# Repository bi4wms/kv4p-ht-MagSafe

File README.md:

# kv4p-ht-MagSafe
MagSafe version for kv4p-ht. Work in progress.

---

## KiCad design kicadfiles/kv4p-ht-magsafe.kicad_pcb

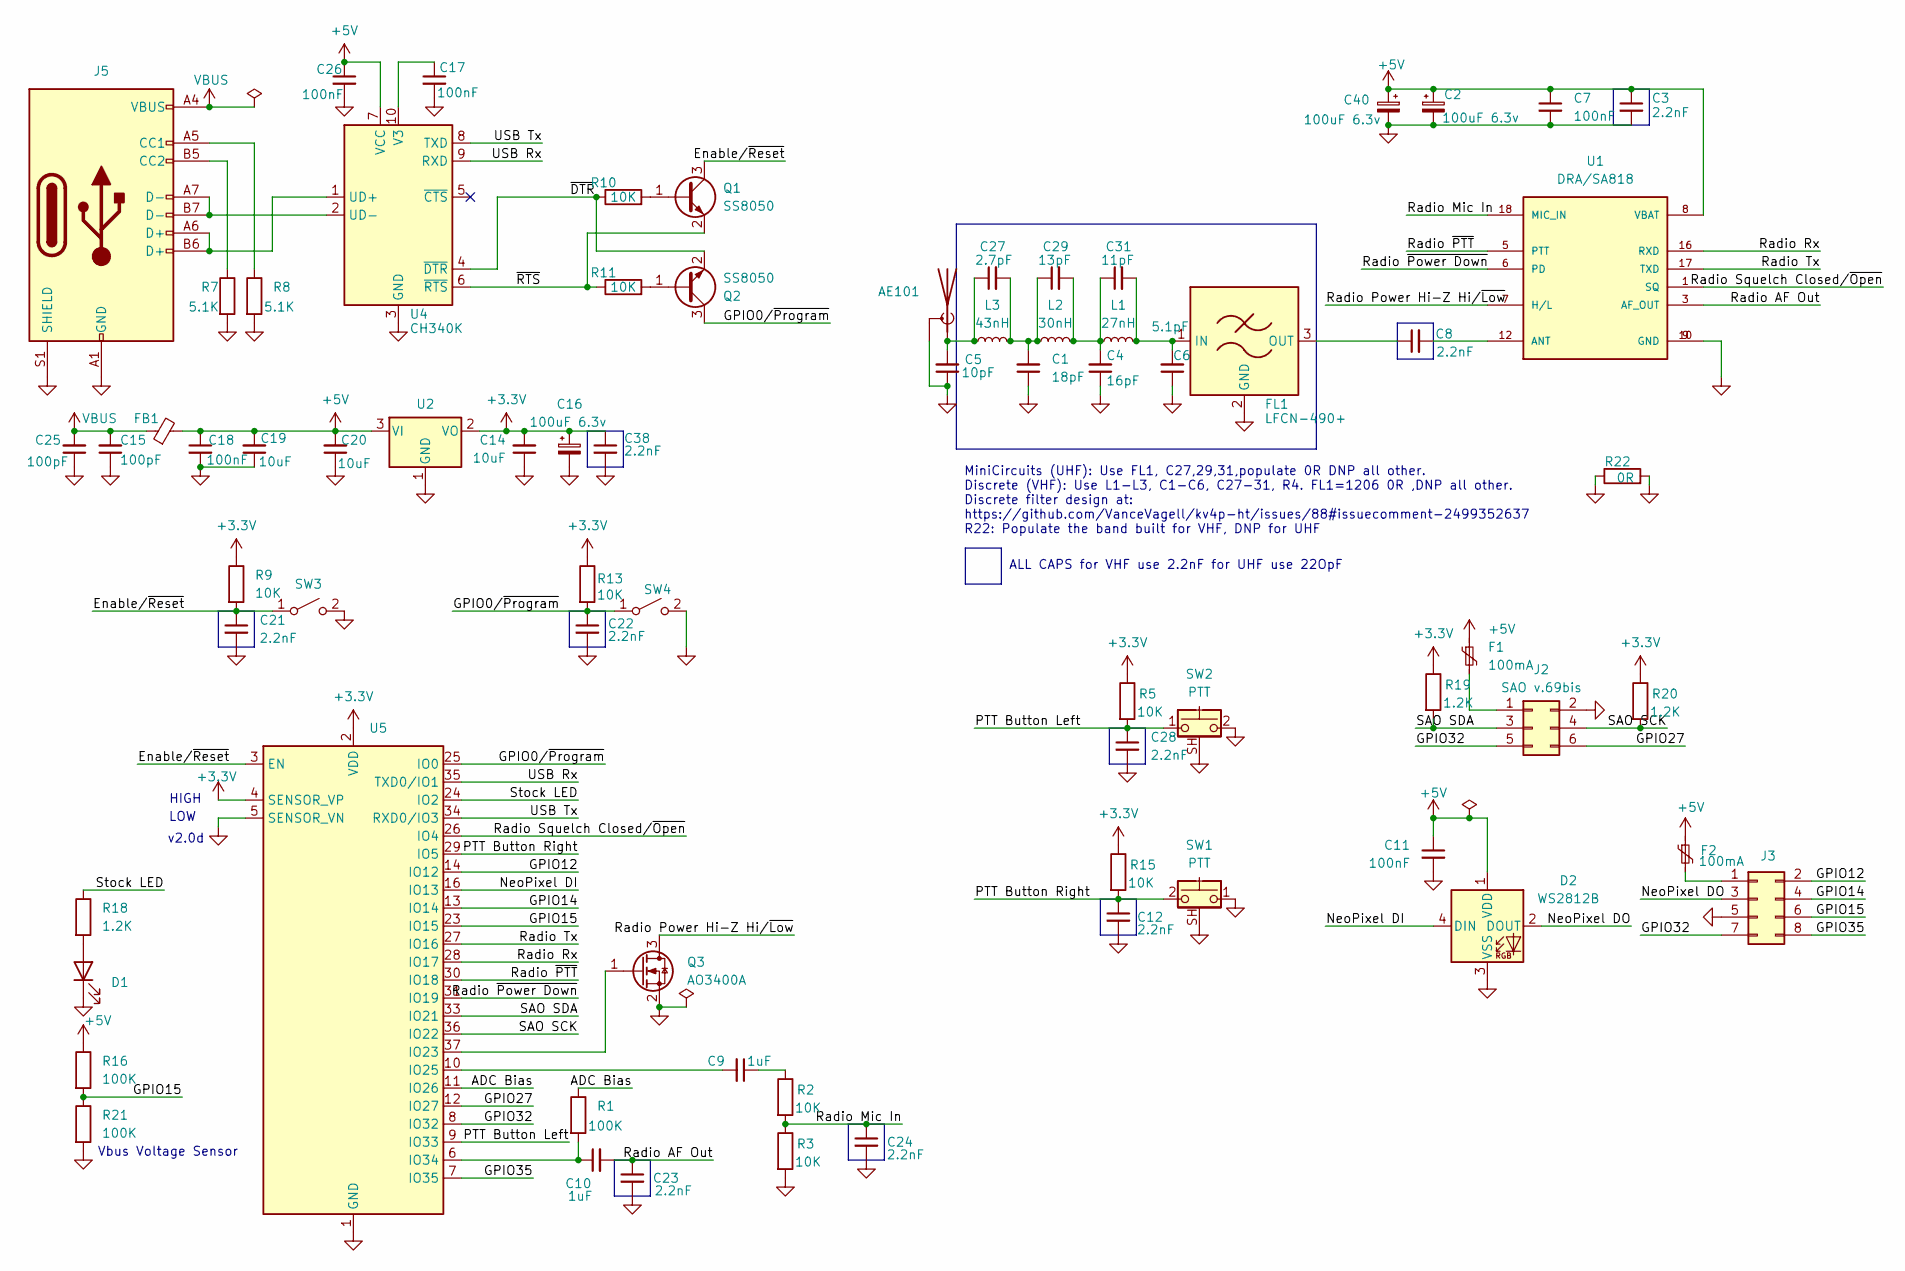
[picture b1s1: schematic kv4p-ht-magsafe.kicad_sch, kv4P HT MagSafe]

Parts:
AE101: Antenna_Shield; SMA_BAT_Wireless_BWSMA-KWE-Z001
C1: 18pF; C_0402_1005Metric; Part Number Ya basic.; LCSC C1549
C2, C16, C40: 100uF 6.3v; C_1206_3216Metric; LCSC C16133
C3, C8, C12, C21, C22, C23, C24, C28, C38: 2.2nF; C_0402_1005Metric; Part Number GCM1885C1H222FA16D; LCSC C2168957
C4: 16pF; C_0402_1005Metric; Part Number CC0402JRNPO9BN160; LCSC C77590
C5: 10pF; C_0402_1005Metric; Part Number Ya so basic.; LCSC C32949
C6: 5.1pF; C_0402_1005Metric; LCSC C60220
C7, C11, C18, C26: 100nF; C_0402_1005Metric; LCSC C14663
C9, C10: 1uF; C_0402_1005Metric; LCSC C15849
C14, C19, C20: 10uF; C_0603_1608Metric; LCSC C15850
C15, C25: 100pF; C_0402_1005Metric; LCSC C14858
C17: 100nF; C_0402_1005Metric; LCSC C15849
C27: 2.7pF; C_0402_1005Metric; LCSC C1561
C29: 13pF; C_0402_1005Metric; LCSC C393681
C31: 11pF; C_0402_1005Metric; LCSC C527000
D1: RED; LED_0603_1608Metric
D2: WS2812B; LED_WS2812B_PLCC4_5.0x5.0mm_P3.2mm
F1, F2: 100mA; C_0402_1005Metric; LCSC C369142
FB1: Ferrite Bead, 1A; L_0603_1608Metric; Part Number BLM18KG102SN1D; LCSC C160982
FL1: LFCN-490+; Filter_Mini-Circuits_FV1206; LCSC C3008205
J2: SAO v.69bis; PinHeader_2x03_P2.54mm_Vertical_SMD; LCSC C192301
J3: GPIO Header; PinHeader_2x04_P2.54mm_Vertical_SMD; LCSC C192300
J5: USB-C Socket; USB_C_Receptacle_HCTL_HC-TYPE-C-16P-01A; LCSC C2894897
L1: 27nH; L_0603_1608Metric; Part Number LQW2BAN27NJ00L; LCSC C1330812
L2: 30nH; L_0603_1608Metric; Part Number LQW2BAN30NG00L; LCSC C3221803
L3: 43nH; L_0603_1608Metric; Part Number LQW2BAN43NG00L; LCSC C1330253
Q1, Q2: SS8050; SOT-23
Q3: AO3400A; SOT-23
R1, R16, R21: 100K; R_0402_1005Metric
R2, R3, R5, R9, R10, R11, R13, R15: 10K; R_0402_1005Metric
R7, R8: 5.1K; R_0402_1005Metric
R18, R19, R20: 1.2K; R_0402_1005Metric
R22: 0R; R_0402_1005Metric
SW1, SW2: PTT; SW-Push-SPST-Horizontal-C782857; LCSC C455252
SW3: Reset; SW_SPST_TL3342; LCSC C318884
SW4: Program; SW_SPST_TL3342; LCSC C318884
U1: DRA/SA818; DORJI_DRA818V; PART_REV 1.23
U2: AZ1117H-3.3TRG1; SOT-223-3_TabPin2; LCSC C110474
U4: CH340K; SSOP-10-1EP_3.9x4.9mm_P1mm_EP2.1x3.3mm
U5: ESP32-WROOM-32E-N4; ESP32-WROOM-32D; LCSC C701341

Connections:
+3.3V: C14.2, C16.1, C38.1, R5.1, R9.1, R13.1, R15.1, R19.1, R20.1, U2.2 (VO), U5.2 (VDD), U5.4 (SENSOR_VP)
+5V: C2.1, C3.1, C7.1, C11.1, C18.1, C19.2, C20.2, C26.1, C40.1, D2.1 (VDD), F1.1, F2.1, FB1.2, R16.1, U1.8 (VBAT), U2.3 (VI), U4.7 (VCC)
/ADC Bias: R1.1, U5.11 (IO26)
/Enable/~Reset: C21.1, Q1.3 (C), R9.2, SW3.1 (A), U5.3 (EN)
/GPIO0/~Program: C22.1, Q2.3 (C), R13.2, SW4.1 (A), U5.25 (IO0)
/GPIO12: J3.2, U5.14 (IO12)
/GPIO14: J3.4, U5.13 (IO14)
/GPIO15: J3.6, R16.2, R21.1, U5.23 (IO15)
/GPIO27: J2.6, U5.12 (IO27)
/GPIO32: J2.5, J3.7, U5.8 (IO32)
/GPIO35: J3.8, U5.7 (IO35)
/NeoPixel DI: D2.4 (DIN), U5.16 (IO13)
/NeoPixel DO: D2.2 (DOUT), J3.3
/PTT Button Left: C28.1, R5.2, SW2.1, U5.9 (IO33)
/PTT Button Right: C12.1, R15.2, SW1.2, U5.29 (IO5)
/Radio AF Out: C10.2, C23.1, U1.3 (AF_OUT)
/Radio Mic In: C24.1, R2.2, R3.1, U1.18 (MIC_IN)
/Radio Power Hi-Z Hi/~Low: Q3.3 (D), U1.7 (H/L)
/Radio Rx: U1.16 (RXD), U5.28 (IO17)
/Radio Squelch Closed/~Open: U1.1 (SQ), U5.26 (IO4)
/Radio Tx: U1.17 (TXD), U5.27 (IO16)
/Radio ~PTT: U1.5 (PTT), U5.30 (IO18)
/Radio ~Power Down: U1.6 (PD), U5.31 (IO19)
/SAO SCK: J2.4, R20.2, U5.36 (IO22)
/SAO SDA: J2.3, R19.2, U5.33 (IO21)
/Stock LED: R18.1, U5.24 (IO2)
/USB Rx: U4.9 (RXD), U5.35 (TXD0/IO1)
/USB Tx: U4.8 (TXD), U5.34 (RXD0/IO3)
/~DTR: Q2.2 (E), R10.1, U4.4 (~DTR)
/~RTS: Q1.2 (E), R11.1, U4.6 (~RTS)
GND: AE101.2 (Shield), C1.1, C2.2, C3.2, C4.1, C5.1, C6.1, C7.2, C11.2, C12.2, C14.1, C15.1, C16.2, C17.2, C18.2, C19.1, C20.1, C21.2, C22.2, C23.2, C24.2, C25.1, C26.2, C28.2, C38.2, C40.2, D1.1 (K), D2.3 (VSS), FL1.2 (GND), FL1.4 (GND), J2.2, J3.5, J5.A1 (GND), J5.A12 (GND), J5.B1 (GND), J5.B12 (GND), J5.S1 (SHIELD), Q3.2 (S), R3.2, R7.2, R8.2, R21.2, R22.1, R22.2, SW1.1, SW1.SH (B), SW2.2, SW2.SH (B), SW3.2 (B), SW4.2 (B), U1.9 (GND), U1.10 (GND), U2.1 (GND), U4.3 (GND), U4.11 (GND), U5.1 (GND), U5.5 (SENSOR_VN), U5.15 (GND), U5.38 (GND), U5.39 (GND)
unnamed: AE101.1 (A), C5.2, C27.1, L3.1
unnamed: C1.2, C27.2, C29.1, L2.1, L3.2
unnamed: C9.1, R2.1
unnamed: C4.2, C29.2, C31.1, L1.1, L2.2
unnamed: D1.2 (A), R18.2
unnamed: C6.2, C31.2, FL1.1 (IN), L1.2
unnamed: C8.1, FL1.3 (OUT)
unnamed: F1.2, J2.1
unnamed: F2.2, J3.1
unnamed: J5.A5 (CC1), R8.1
unnamed: J5.B5 (CC2), R7.1
unnamed: Q1.1 (B), R10.2
unnamed: Q2.1 (B), R11.2
unnamed: Q3.1 (G), U5.37 (IO23)
unnamed: C8.2, U1.12 (ANT)
unnamed: J5.A6 (D+), J5.B6 (D+), U4.1 (UD+)
unnamed: J5.A7 (D-), J5.B7 (D-), U4.2 (UD-)
unnamed: C17.1, U4.10 (V3)
unnamed: C9.2, U5.10 (IO25)
unnamed: C10.1, R1.2, U5.6 (IO34)
VBUS: C15.2, C25.2, FB1.1, J5.A4 (VBUS), J5.A9 (VBUS), J5.B4 (VBUS), J5.B9 (VBUS)

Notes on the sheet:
MiniCircuits (UHF): Use FL1, C27,29,31,populate 0R DNP all other. Discrete (VHF): Use L1-L3, C1-C6, C27-31, R4. FL1=1206 0R ,DNP all other. Discrete filter design at: https://github.com/VanceVagell/kv4p-ht/issues/88#issuecomment-2499352637 R22: Populate the band built for VHF, DNP for UHF
ALL CAPS for VHF use 2.2nF for UHF use 22OpF
v2.0d
LOW
HIGH
Vbus Voltage Sensor

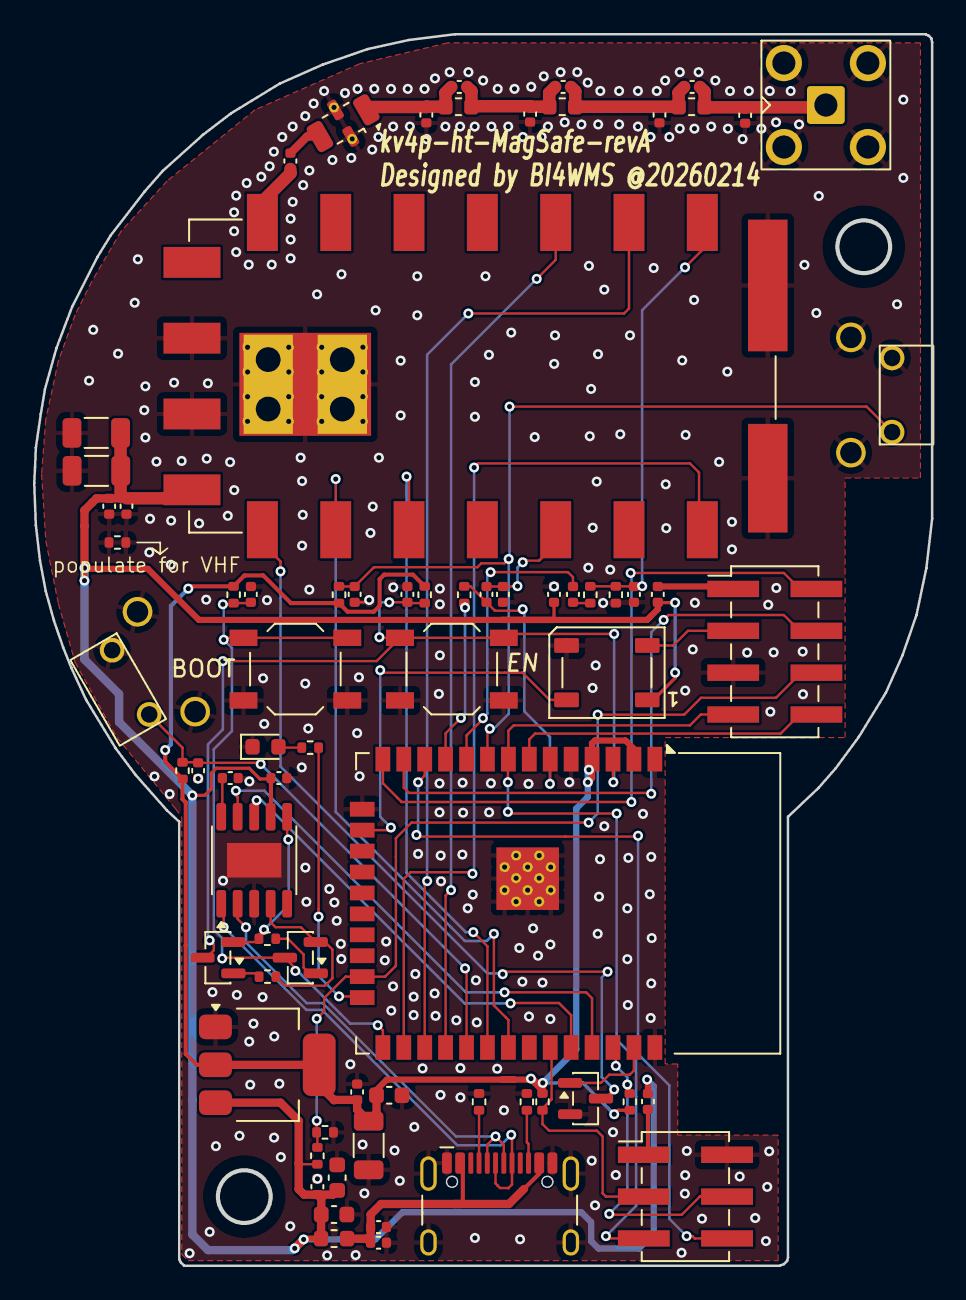
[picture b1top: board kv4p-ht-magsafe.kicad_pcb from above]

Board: 2 copper layers, 54.4 x 74.6 mm, 72 parts (0 on the bottom side), 52 nets.

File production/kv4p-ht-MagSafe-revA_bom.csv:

Designator,Footprint,Quantity,Value,LCSC Part #
AE101,SMA_BAT_Wireless_BWSMA-KWE-Z001,1,Antenna_Shield,
C1,0402,1,18pF,C1549
"C10, C9",0402,2,1uF,C15849
"C11, C18, C26, C7",0402,4,100nF,C14663
"C12, C21, C22, C23, C24, C28, C3, C38, C8",0402,9,2.2nF,C2168957
"C14, C19, C20",0603,3,10uF,C15850
"C15, C25",0402,2,100pF,C14858
"C16, C2, C40",1206,3,100uF 6.3v,C16133
C17,0402,1,100nF,C15849
C27,0402,1,2.7pF,C1561
C29,0402,1,13pF,C393681
C31,0402,1,11pF,C527000
C4,0402,1,16pF,C77590
C5,0402,1,10pF,C32949
C6,0402,1,5.1pF,C60220
D1,0603,1,RED,C2286
D2,LED_WS2812_PLCC6_5.0x5.0mm_P1.6mm,1,WS2812,
"F1, F2",0402,2,100mA,C369142
FB1,0603,1,"Ferrite Bead, 1A",C160982
FL1,Filter_Mini-Circuits_FV1206,1,LFCN-490+,C3008205
J2,PinHeader_2x03_P2.54mm_Vertical_SMD,1,SAO v.69bis,C192301
J3,PinHeader_2x04_P2.54mm_Vertical_SMD,1,GPIO Header,C192300
J5,USB_C_Receptacle_HCTL_HC-TYPE-C-16P-01A,1,USB-C Socket,C2894897
L1,0603,1,27nH,C1330812
L2,0603,1,30nH,C3221803
L3,0603,1,43nH,C1330253
"Q1, Q2",SOT-23,2,SS8050,C2150
Q3,SOT-23,1,AO3400A,
"R1, R16, R21",0402,3,100K,C25803
"R10, R11, R13, R15, R2, R5, R9",0402,7,10K,C25804
"R18, R19, R20",0402,3,1.2K,C22765
R22,0402,1,0R,C17888
R3,0402,1,10K,C22765
R6,0402,1,150R,C22765
"R7, R8",0402,2,5.1K,C26000
"SW1, SW2",SW-Push-SPST-Horizontal-C782857,2,PTT,C455252
SW3,SW_SPST_TL3342,1,Reset,C318884
SW4,SW_SPST_TL3342,1,Program,C318884
U1,DORJI_DRA818V,1,DRA/SA818,
U2,SOT-223-3_TabPin2,1,AZ1117H-3.3TRG1,C110474
U4,SSOP-10-1EP_3.9x4.9mm_P1mm_EP2.1x3.3mm,1,CH340K,
U5,ESP32-WROOM-32D,1,ESP32-WROOM-32E-N4,C701341

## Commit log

2026-02-24 Add Ko-fi button and update image in README
2026-02-24 Add PayPal badge to README
2026-02-24 Update README with donation links
    Added donation options for support.
2026-05-03 Update README with 3D case images
    Added images to README for visual representation.
